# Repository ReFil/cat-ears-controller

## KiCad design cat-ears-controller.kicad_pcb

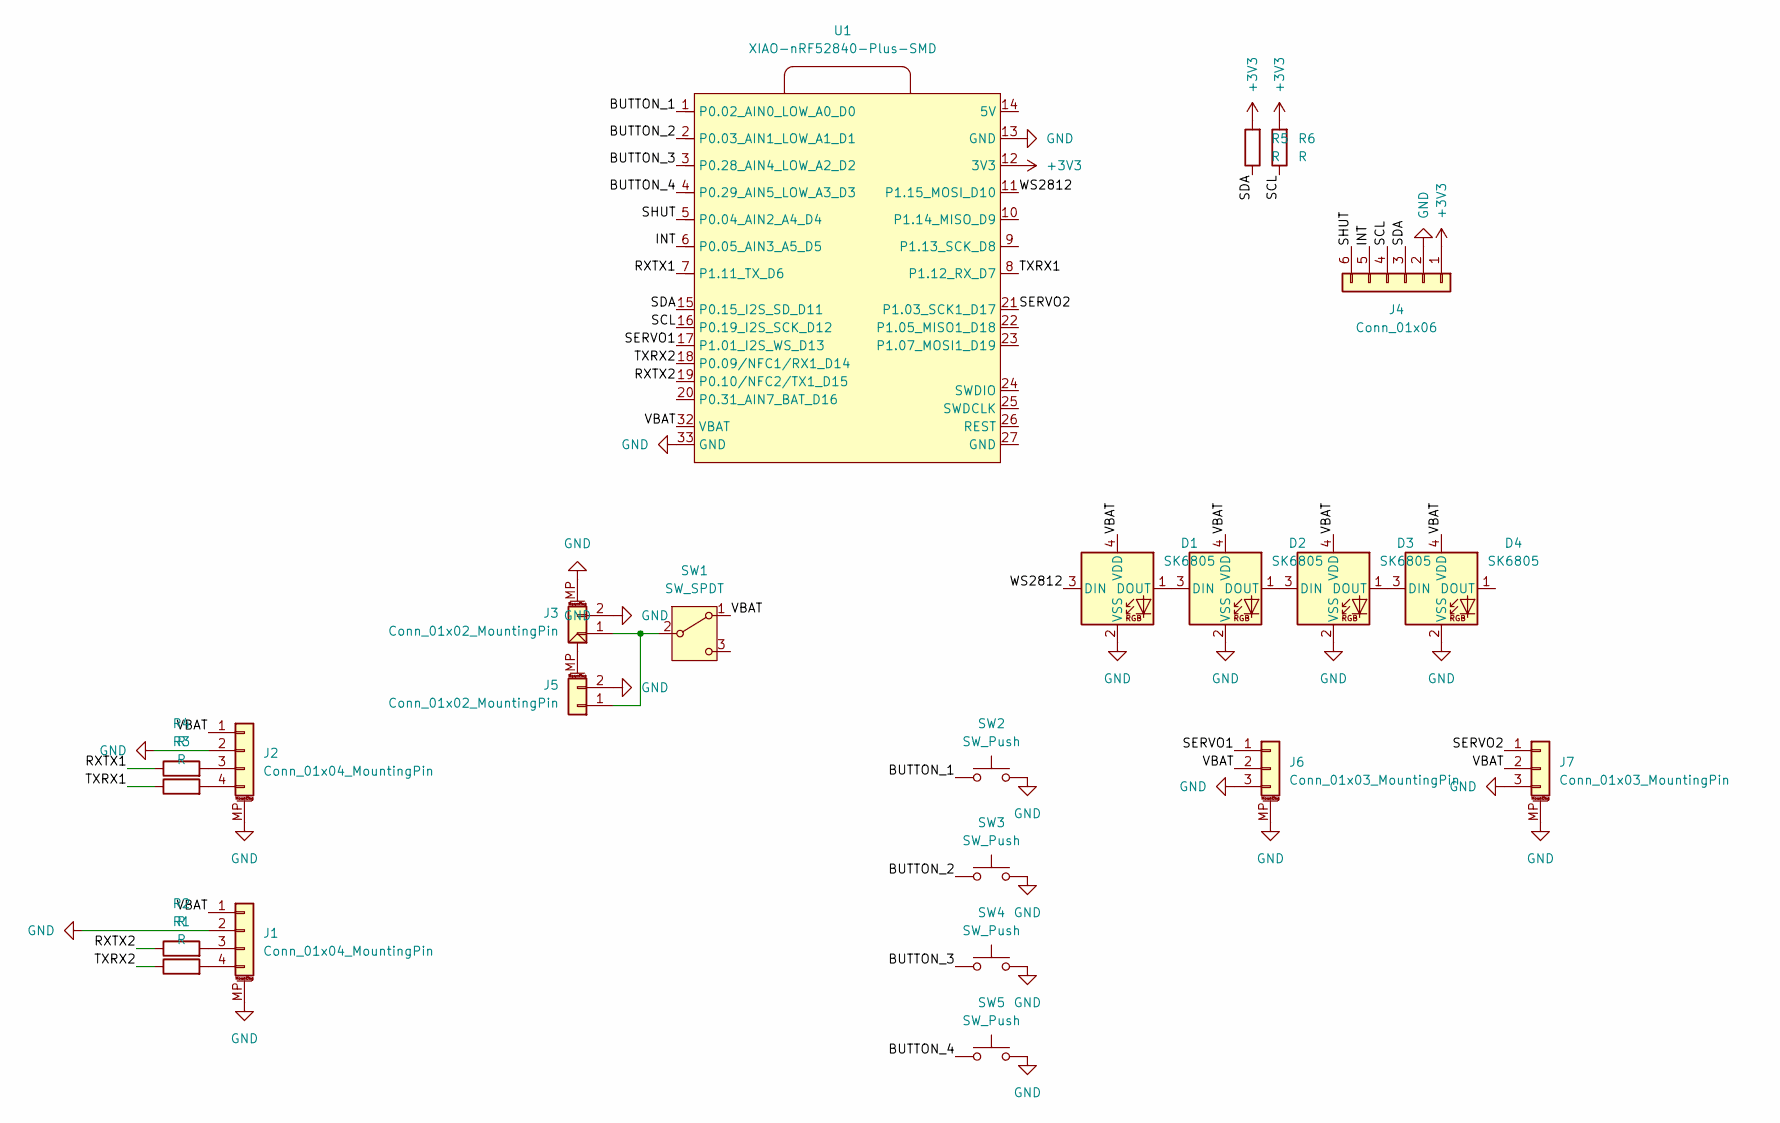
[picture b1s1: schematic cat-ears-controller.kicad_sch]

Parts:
D1, D2, D3, D4: SK6805; LED_SK6812_EC15_1.5x1.5mm
J1, J2: Conn_01x04_MountingPin; Molex_Pico-EZmate_78171-0004_1x04-1MP_P1.20mm_Vertical; LCSC Part C2840019
J3, J5: Conn_01x02_MountingPin; JST_SH_BM02B-SRSS-TB_1x02-1MP_P1.00mm_Vertical
J4: Conn_01x06; PinSocket_1x06_P2.54mm_Vertical
J6, J7: Conn_01x03_MountingPin; JST_ZH_B3B-ZR-SM4-TF_1x03-1MP_P1.50mm_Vertical
R1, R2, R3, R4, R5, R6: R; R_0603_1608Metric
SW1: SW_SPDT; SW_SPDT_PCM12
SW2, SW3, SW4, SW5: SW_Push; SW_Push_1P1T_NO_CK_KMR2
U1: XIAO-nRF52840-Plus-SMD

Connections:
+3V3: J4.1, R5.2, R6.2, U1.12 (3V3)
/BUTTON_1: SW2.1, U1.1 (P0.02_AIN0_LOW_A0_D0)
/BUTTON_2: SW3.1, U1.2 (P0.03_AIN1_LOW_A1_D1)
/BUTTON_3: SW4.1, U1.3 (P0.28_AIN4_LOW_A2_D2)
/BUTTON_4: SW5.1, U1.4 (P0.29_AIN5_LOW_A3_D3)
/INT: J4.5, U1.6 (P0.05_AIN3_A5_D5)
/RXTX1: R4.1, U1.7 (P1.11_TX_D6)
/RXTX2: R2.1, U1.19 (P0.10/NFC2/TX1_D15)
/SCL: J4.4, R6.1, U1.16 (P0.19_I2S_SCK_D12)
/SDA: J4.3, R5.1, U1.15 (P0.15_I2S_SD_D11)
/SERVO1: J6.1, U1.17 (P1.01_I2S_WS_D13)
/SERVO2: J7.1, U1.21 (P1.03_SCK1_D17)
/SHUT: J4.6, U1.5 (P0.04_AIN2_A4_D4)
/TXRX1: R3.1, U1.8 (P1.12_RX_D7)
/TXRX2: R1.1, U1.18 (P0.09/NFC1/RX1_D14)
/VBAT: D1.4 (VDD), D2.4 (VDD), D3.4 (VDD), D4.4 (VDD), J1.1, J2.1, J6.2, J7.2, SW1.1 (A), U1.32 (VBAT)
/WS2812: D1.3 (DIN), U1.11 (P1.15_MOSI_D10)
GND: D1.2 (VSS), D2.2 (VSS), D3.2 (VSS), D4.2 (VSS), J1.2, J1.MP (MountPin), J2.2, J2.MP (MountPin), J3.2, J3.MP (MountPin), J4.2, J5.2, J5.MP (MountPin), J6.3, J6.MP (MountPin), J7.3, J7.MP (MountPin), SW2.2, SW3.2, SW4.2, SW5.2, U1.13 (GND), U1.33 (GND)
unnamed: D1.1 (DOUT), D2.3 (DIN)
unnamed: D2.1 (DOUT), D3.3 (DIN)
unnamed: D3.1 (DOUT), D4.3 (DIN)
unnamed: J1.3, R2.2
unnamed: J1.4, R1.2
unnamed: J2.3, R4.2
unnamed: J2.4, R3.2
unnamed: J3.1, J5.1, SW1.2 (B)

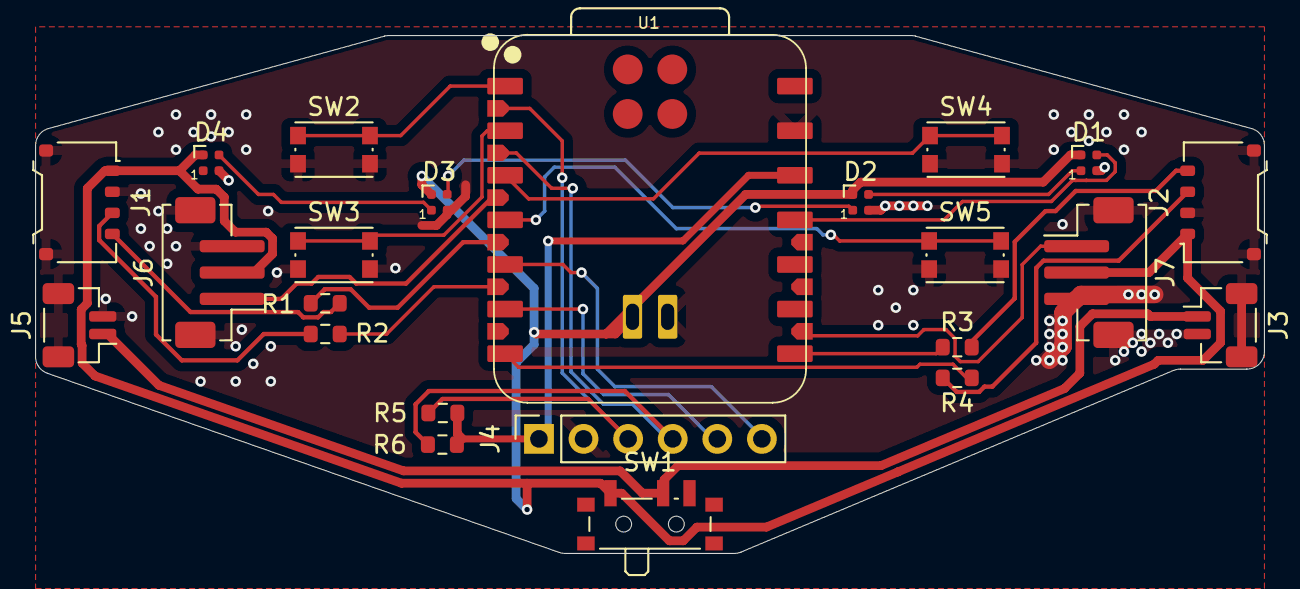
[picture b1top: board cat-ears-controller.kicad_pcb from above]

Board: 2 copper layers, 70.0 x 29.5 mm, 23 parts (0 on the bottom side), 26 nets.

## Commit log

2025-12-29 complete routing
2026-01-11 Commit cat ears controller pcb
2026-02-07 Add servo connectors
2026-06-24 outputs
